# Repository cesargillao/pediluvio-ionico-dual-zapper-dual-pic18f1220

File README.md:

# Dual Pediluvio Iónico con Zapper (PIC18F1220)

## Se proporciona:
* Diagrama esquemático para emular el funcionamiento (Proteus)
* Diagrama esquemático y PCB (CadSoft Eagle)
* Software en C y ASM con su respectivo HEX (CCS Compiler)

### Si te gusta el proyecto, recomiendo dejar una estrella en el mismo o en mi perfil.
### Eso me inspira a seguir colaborando a la comunidad ❤.

# ⚠ Advertencia ⚠ 
### Este producto no ha sido probado más allá de una emulación mediante software y fue desarrollado con fines educativos. Por lo tanto, el uso que se le quiera dar a este proyecto es responsabilidad de quien lo implemente.

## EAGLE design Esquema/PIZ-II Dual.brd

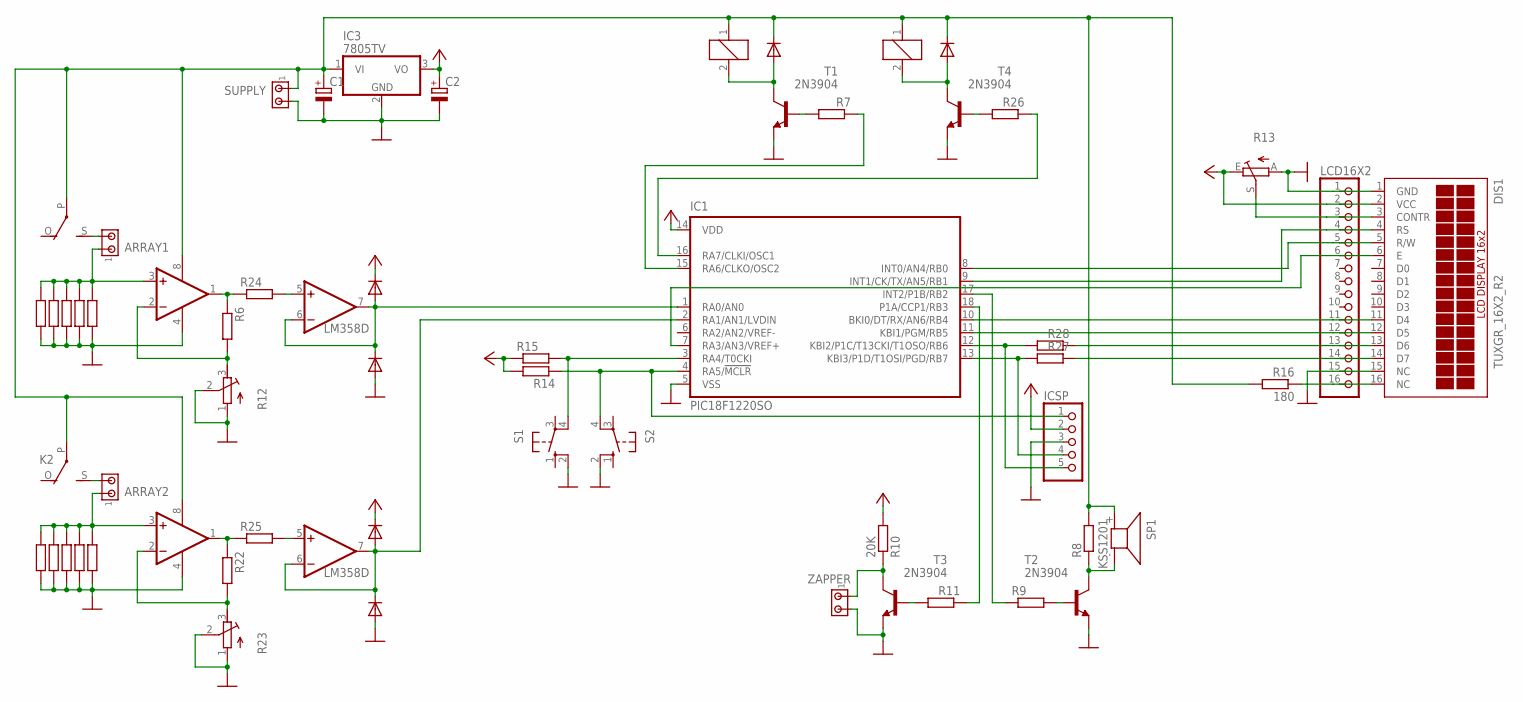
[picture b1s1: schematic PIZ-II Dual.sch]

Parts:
ARRAY1, ARRAY2: MTA02-100; 10X02MTA
C1, C2: CPOL-EUE2.5-7; E2,5-7
D1, D2, D3, D4, D5, D6: 1N4148DO35-7; DO35-7
DIS1: TUXGR_16X2_R2
IC1: PIC18F1220SO; SO-18W
IC2, IC4: LM358D; SO08
IC3: 7805TV; TO220V
ICSP: PINHD-1X55X2MM; 1_05X2MM
K1, K2: G5L; G5LE
LCD16X2: PINHD-1X16; 1X16
R1, R2, R3, R4, R5, R8, R17, R18, R19, R20, R21: R-EU_R1210; R1210
R6, R7, R9, R11, R14, R15, R22, R24, R25, R26, R27, R28: R-EU_R1206; R1206
R10: 20K; R1206
R12, R23: R-TRIMM64W; RTRIM64W
R13: TRIM_EU-CA6V; CA6V
R16: 180; R2512
S1, S2: 10-XX; B3F-10XX
SP1: KSS1201
SUPPLY: MTA02-100; 10X02MTA
T1, T2, T3, T4: 2N3904; TO92
ZAPPER: MTA02-100; 10X02MTA

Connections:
GND: C1.-, C2.-, D2.A, D5.A, DIS1.1 (GND), DIS1.15 (NC), IC1.5 (VSS), IC2.4 (V-), IC3.2 (GND), IC4.4 (V-), ICSP.3, LCD16X2.1, LCD16X2.15, R1.2, R2.2, R3.2, R4.2, R5.2, R12.1 (A), R12.2 (S), R13.A, R17.2, R18.2, R19.2, R20.2, R21.2, R23.1 (A), R23.2 (S), S1.2 (S1), S2.2 (S1), SUPPLY.2, T1.3 (E), T2.3 (E), T3.3 (E), T4.3 (E), ZAPPER.2
unnamed: ARRAY1.1, IC2.3 (+IN), R1.1, R2.1, R3.1, R4.1, R5.1
unnamed: ARRAY1.2, K1.S
unnamed: IC2.1 (OUT), R6.1, R24.1
unnamed: IC2.2 (-IN), R6.2, R12.3 (E)
unnamed: R8.1, SP1.- (2), T2.1 (C)
unnamed: D1.A, D2.C, IC1.1 (RA0/AN0), IC2.6 (-IN), IC2.7 (OUT)
unnamed: D3.A, K1.2, T1.1 (C)
unnamed: R10.1, T3.1 (C), ZAPPER.1
unnamed: R7.2, T1.2 (B)
unnamed: R9.2, T2.2 (B)
unnamed: R11.2, T3.2 (B)
unnamed: IC1.17 (INT2/P1B/RB2), R9.1
unnamed: DIS1.4 (RS), IC1.9 (INT1/CK/TX/AN5/RB1), LCD16X2.4
unnamed: IC1.15 (RA6/CLKO/OSC2), R7.1
unnamed: DIS1.14 (D7), LCD16X2.14, R27.1
unnamed: DIS1.13 (D6), LCD16X2.13, R28.1
unnamed: DIS1.12 (D5), IC1.11 (KBI1/PGM/RB5), LCD16X2.12
unnamed: DIS1.11 (D4), IC1.10 (BKI0/DT/RX/AN6/RB4), LCD16X2.11
unnamed: ARRAY2.1, IC4.3 (+IN), R17.1, R18.1, R19.1, R20.1, R21.1
unnamed: IC1.18 (P1A/CCP1/RB3), R11.1
unnamed: DIS1.6 (E), IC1.7 (RA3/AN3/VREF+), LCD16X2.6
unnamed: DIS1.3 (CONTR), LCD16X2.3, R13.S
unnamed: DIS1.5 (R/W), IC1.8 (INT0/AN4/RB0), LCD16X2.5
unnamed: C1.+, D3.C, D6.C, IC2.8 (V+), IC3.1 (VI), IC4.8 (V+), K1.1, K1.P, K2.1, K2.P, R8.2, R16.2, SP1.+ (1), SUPPLY.1
unnamed: DIS1.16 (NC), LCD16X2.16, R16.1
unnamed: IC1.12 (KBI2/P1C/T13CKI/T1OSO/RB6), ICSP.5, R28.2
unnamed: IC1.13 (KBI3/P1D/T1OSI/PGD/RB7), ICSP.4, R27.2
unnamed: IC4.1 (OUT), R22.1, R25.1
unnamed: IC4.2 (-IN), R22.2, R23.3 (E)
unnamed: D4.A, D5.C, IC1.2 (RA1/AN1/LVDIN), IC4.6 (-IN), IC4.7 (OUT)
unnamed: ARRAY2.2, K2.S
unnamed: IC2.5 (+IN), R24.2
unnamed: IC4.5 (+IN), R25.2
unnamed: IC1.3 (RA4/T0CKI), R15.2, S1.4 (P1)
unnamed: D6.A, K2.2, T4.1 (C)
unnamed: R26.2, T4.2 (B)
unnamed: IC1.16 (RA7/CLKI/OSC1), R26.1
unnamed: IC1.4 (RA5/!MCLR), ICSP.1, R14.1, S2.4 (P1)
VCC: C2.+, D1.C, D4.C, DIS1.2 (VCC), IC1.14 (VDD), IC3.3 (VO), ICSP.2, LCD16X2.2, R10.2, R13.E, R14.2, R15.1

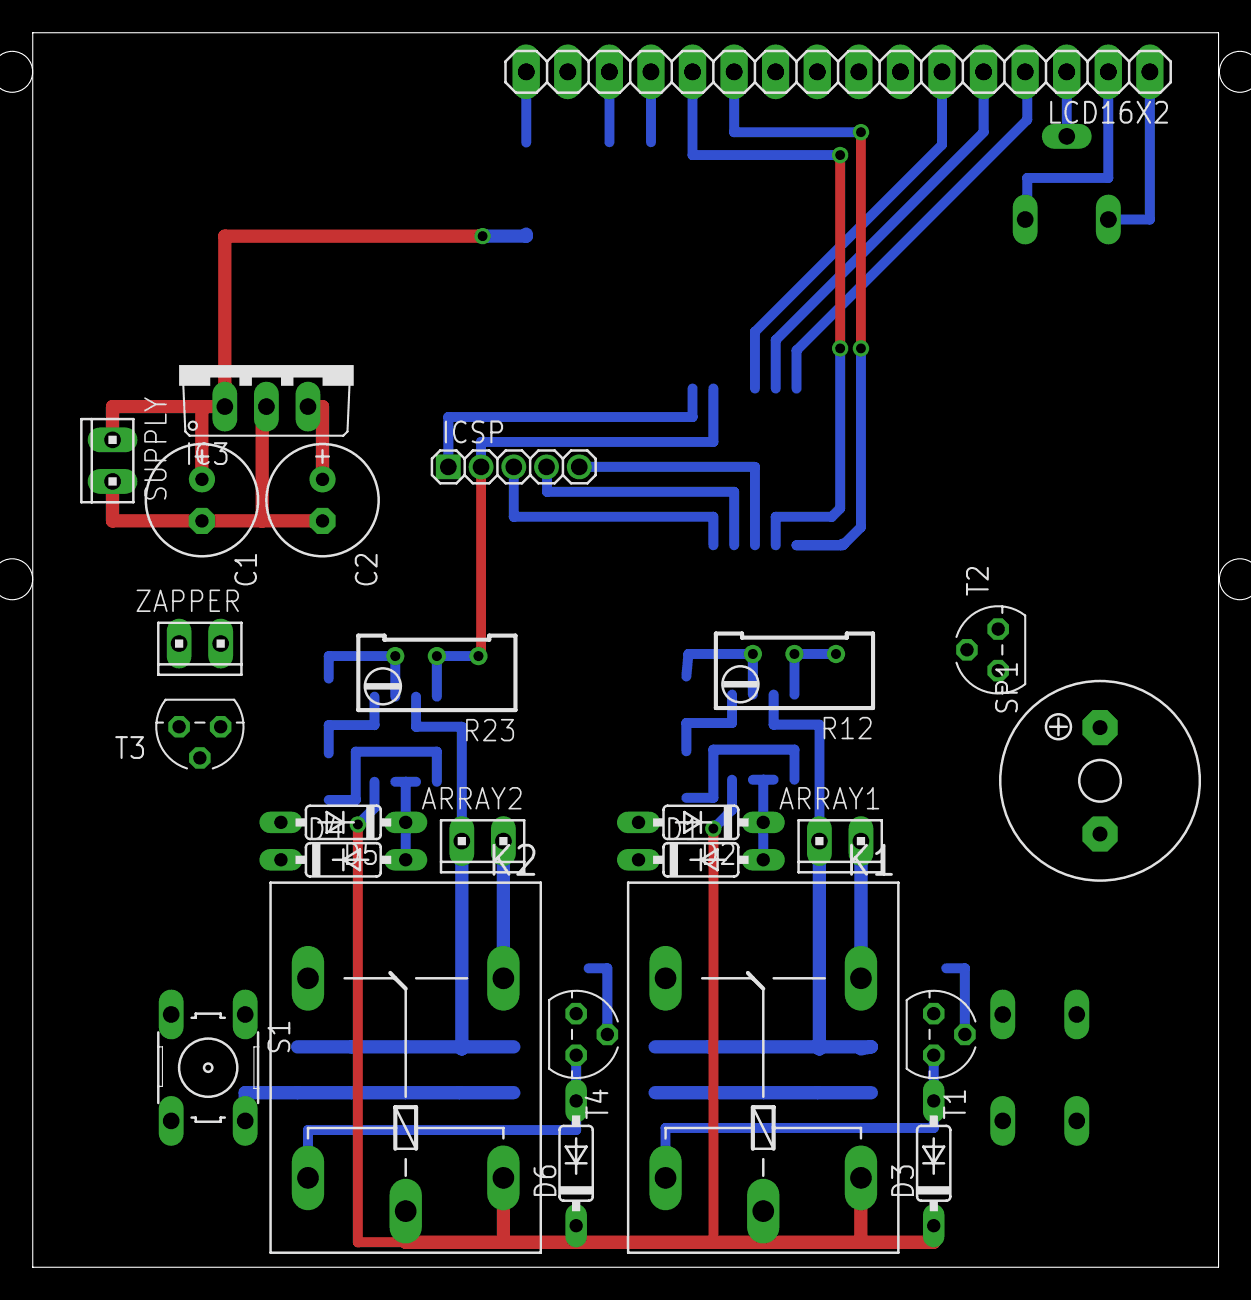
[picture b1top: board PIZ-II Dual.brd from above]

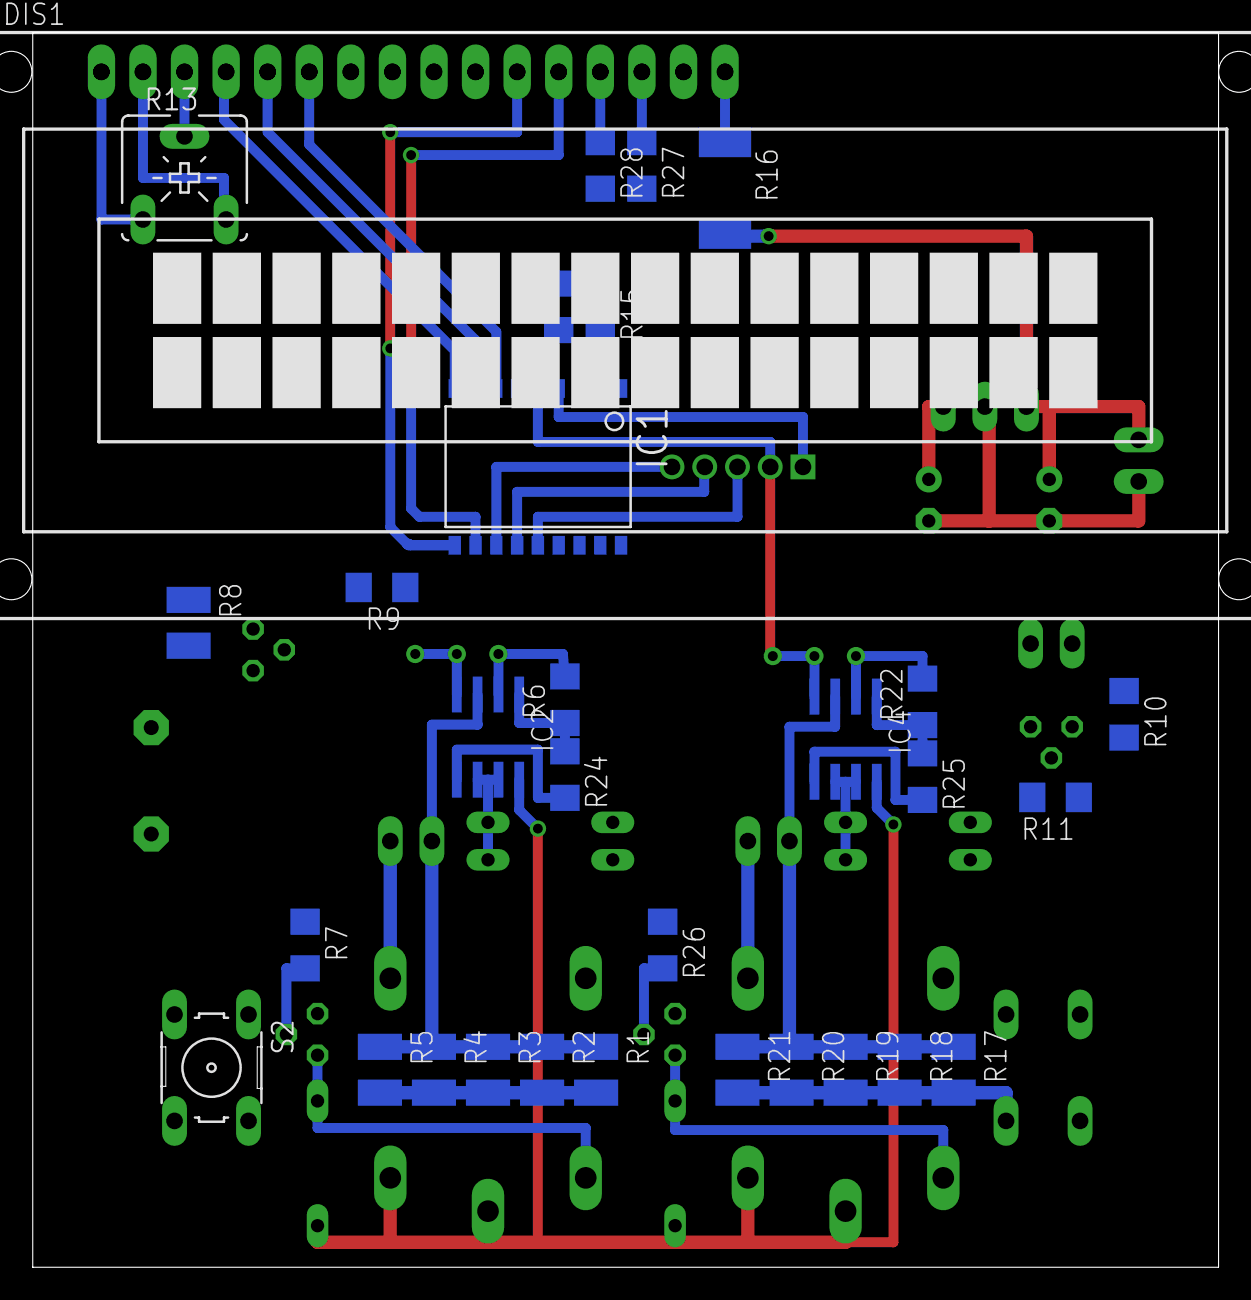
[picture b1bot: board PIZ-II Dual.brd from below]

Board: 2 copper layers, 72.4 x 75.4 mm, 56 parts (31 on the bottom side), 40 nets.
